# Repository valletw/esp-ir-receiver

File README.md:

# ESP32 Infra-Red Receiver

This project is made to receive IR transmitter information (TV remote) and
control something over WiFi. This project will be used for
[UPnP remote controller project](https://github.com/valletw/esp-upnp-remote).

## Hardware

Four status LED are available:

- `PWR`: 3.3V state
- `BT`: Bluetooth / BLE pairing status
- `WIFI`: WiFi connection status
- `STAT`: Software protocol status

Two buttons are available:

- `BOOT`: Control processor download mode on boot
- `EN`: Control processor reset

For advanced debug, test points are available for JTAG probe and UART controller.

*Note: 3D shapes were not fully configured on my setup, so some components are not
displayed in the render, to be fix.*

### Components choice

This project is based on an ESP32-C3 SoC: `ESP8685H4` (4 MB Flash with no
PSRAM). ESP32 has been selected for the WiFi & Bluetooth support and the big
community to generate easily a software. The choice of "C3" is to ensure support
with the SDK for longer time and minimal footprint. ESP32 modules have not been
kept due to PCB assembly fees. Espressif hardware design rules has been take into
account following there
[documentation](https://docs.espressif.com/projects/esp-hardware-design-guidelines/en/latest/esp32c3/pcb-layout-design.html)

USB-UART bridge has not been added to reduce the number of component. The ESP32
support direct USB connection to manage debug mode with firmware download, and
UART communication.

The 3.3V to power all the components is generated from an LDO using the 5V of the
USB socket.

All others components has been selected from [JLCPCB](https://jlcpcb.com/parts/)
catalogue to minimize the cost and the assembly fees.

### Manufacturing

The board is manufactured by [JLCPCB](https://jlcpcb.com), here is the details
you will require to generate an order.

*Note: JLCPCB requests some modifications on output files, do not use direct
export from KiCad (check the FAQ)*

#### PCB

Files: [Gerbers](jlcpcb/gerbers.zip)

Configuration              | Value
---------------------------|---------------------------------
Base Materiel              | FR-4
Layers                     | 4
Dimensions                 | 33.14 x 21.45
Different design           | 1
Delivery format            | Single PCB
PCB thickness              | 1.6
PCB color                  | Green (other colors have fees)
Silkscreen                 | White
Materiel type              | FR4-Standard TG 135-140
Surface finish             | HASL
Specify layer sequence     | F_Cu / In1_Cu / In2_Cu / B_Cu
Impedance control          | Yes
Layer stack-up             | JLC04161H-7628
Via covering               | Tented or Plugged
Min via hole size/diameter | 0.3mm/0.4mm
Remove order number        | Specify a location

*Note: All options have not been detail here, keep default value.*

#### Assembly

Files: [BOM](jlcpcb/bom.csv), [CPL](jlcpcb/cpl.csv)

Configuration       | Value
--------------------|--------------------
PCBA type           | Economic
Assembly side       | Top
Tooling holes       | Added by JLCPCB

Verify "pick & place" orientations and positions on the web viewer

JLCPCB will add 2 tooling holes for assembly (1 mm diameter near the board corners).

*Note: All options have not been detail here, keep default value.*

### ESP32 Pinout

For those who want to reuse this project, here is the ESP32 pinout to manage the
different input/output.

Name              | Pin  | Direction
------------------|------|----------
IR Rx             | IO3  | Input
WiFi status       | IO0  | Output
Bluetooth status  | IO1  | Output
Software status   | IO10 | Output

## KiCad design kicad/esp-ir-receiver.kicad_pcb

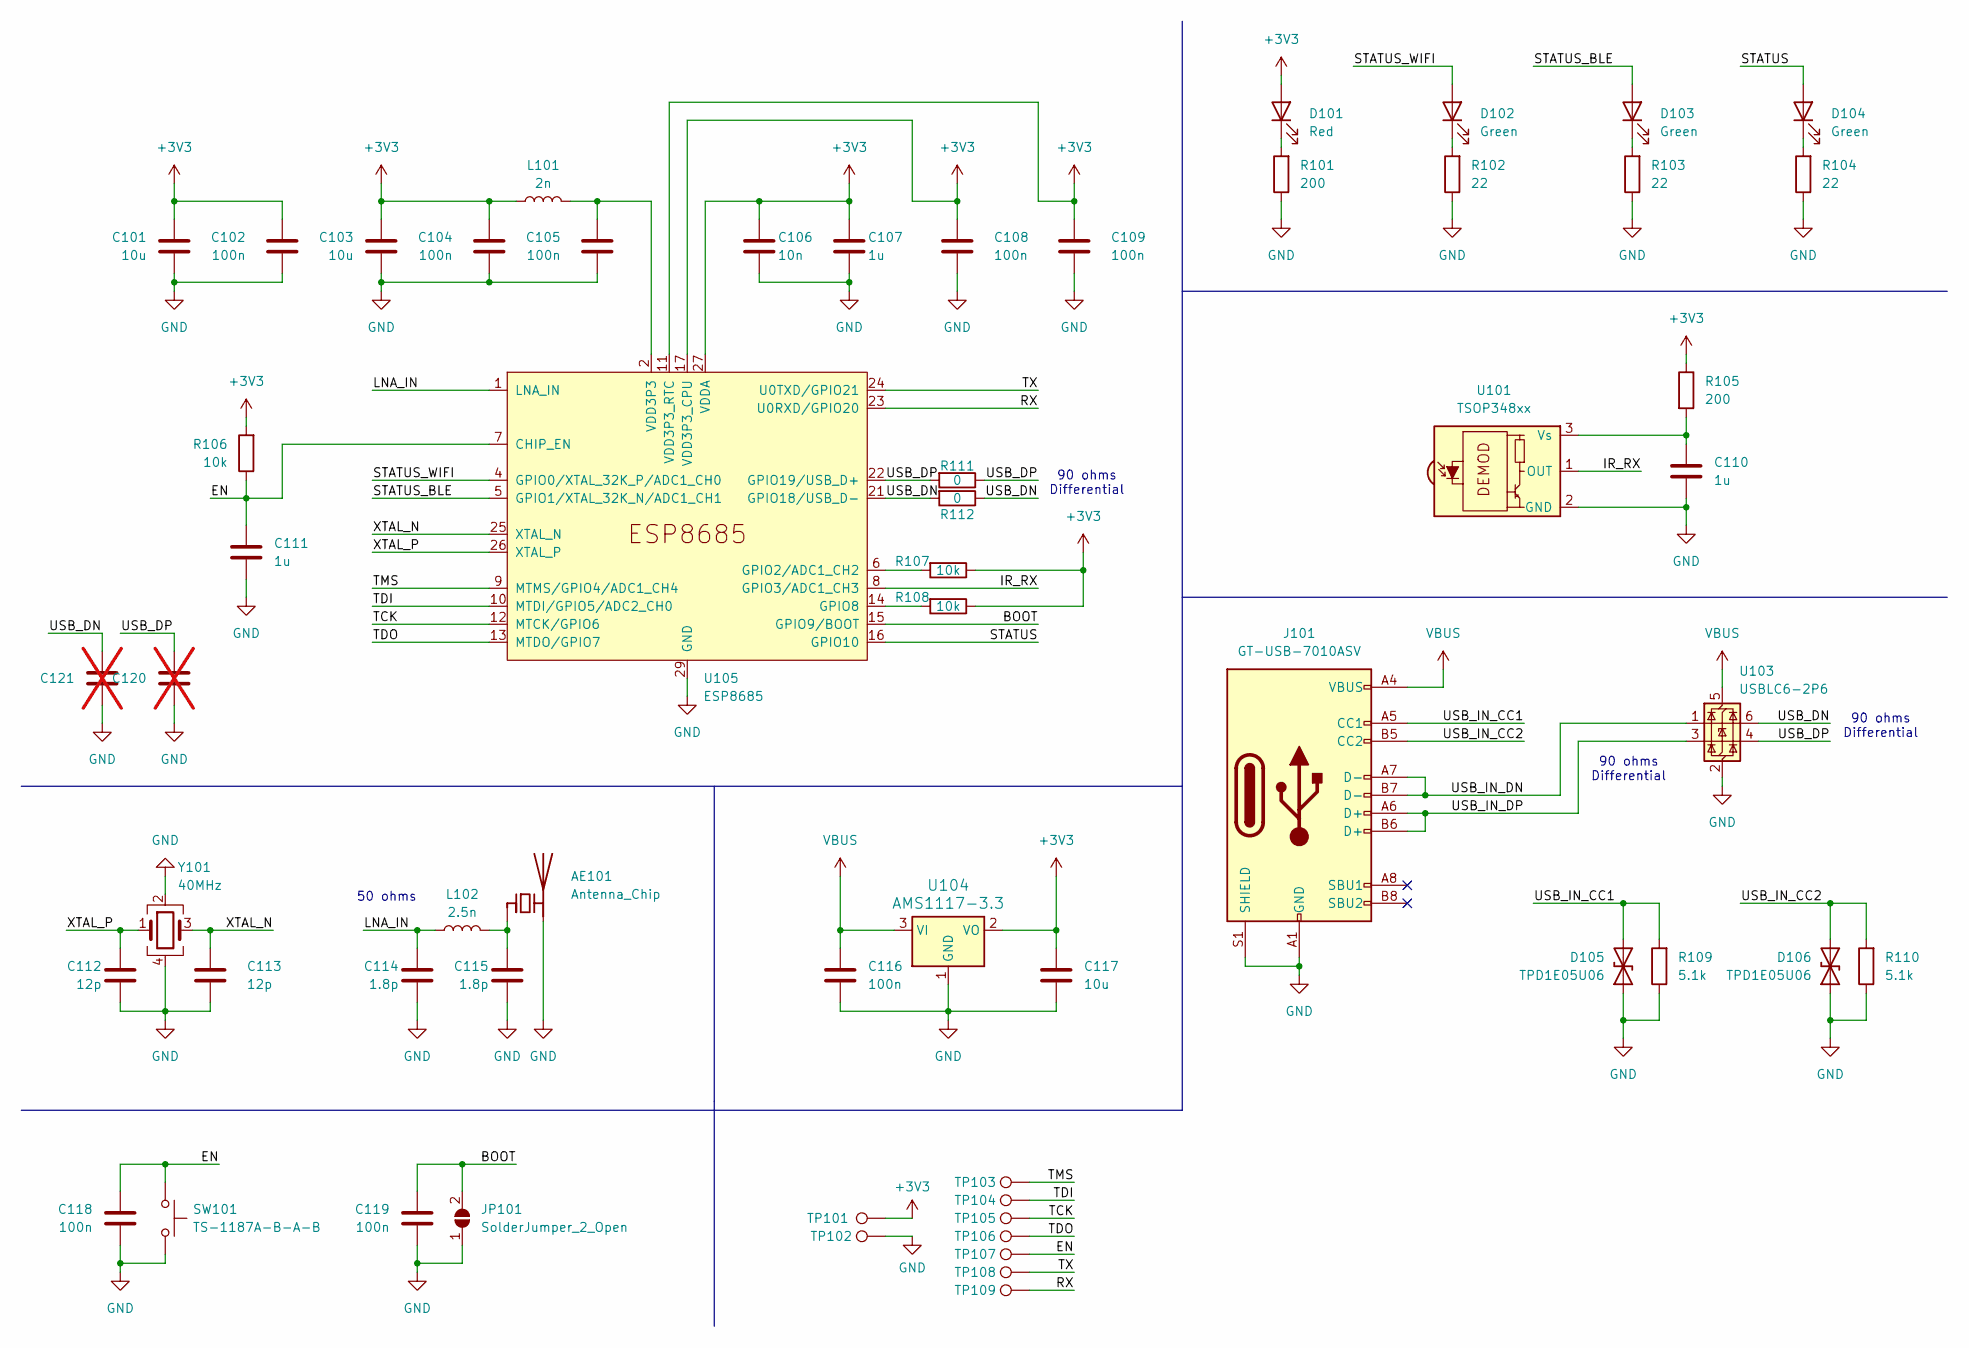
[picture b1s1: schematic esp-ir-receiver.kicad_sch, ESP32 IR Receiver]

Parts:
AE101: Antenna_Chip; Texas_SWRA117D_2.4GHz_Left
C101, C103, C117: 10u; C_0402_1005Metric; MFR Part# CL05A106MQ5NUNC; JLCPCB Part# C15525
C102, C104, C105, C108, C109, C116, C118, C119: 100n; C_0402_1005Metric; MFR Part# CL05B104KO5NNNC; JLCPCB Part# C1525
C106: 10n; C_0402_1005Metric; MFR Part# CL05B103KB5NNNC; JLCPCB Part# C15195
C107, C110, C111: 1u; C_0402_1005Metric; MFR Part# CL05A105KA5NQNC; JLCPCB Part# C52923
C112, C113: 12p; C_0402_1005Metric; MFR Part# 0402CG120J500NT; JLCPCB Part# C1547
C114, C115: 1.8p; C_0402_1005Metric; MFR Part# 0402CG1R8C500NT; JLCPCB Part# C1553
C120, C121: C_0402_1005Metric; not fitted
D101: Red; LED_0603_1608Metric; MFR Part# KT-0603R; JLCPCB Part# C2286
D102, D103, D104: Green; LED_0603_1608Metric; MFR Part# 19-217/GHC-YR1S2/3T; JLCPCB Part# C72043
D105, D106: TPD1E05U06; Texas_DPY0002A_0.6x1mm_P0.65mm; MFR Part# TPD1E05U06DPYR; JLCPCB Part# C436349
J101: GT-USB-7010ASV; USB_C_Receptacle_G-Switch_GT-USB-7010ASV; MFR Part# GT-USB-7010ASV; JLCPCB Part# C2988369
JP101: SolderJumper_2_Open; SolderJumper-2_P1.3mm_Open_RoundedPad1.0x1.5mm
L101: 2n; L_0402_1005Metric; MFR Part# LQG15HS2N0S02D; JLCPCB Part# C18216
L102: 2.5n; L_0402_1005Metric; MFR Part# LQW15AN2N5B00D; JLCPCB Part# C237342
R101, R105: 200; R_0402_1005Metric; MFR Part# 0402WGF2000TCE; JLCPCB Part# C25087
R102, R103, R104: 22; R_0402_1005Metric; MFR Part# 0402WGF220JTCE; JLCPCB Part# C25092
R106, R107, R108: 10k; R_0402_1005Metric; MFR Part# 0402WGF1002TCE; JLCPCB Part# C25744
R109, R110: 5.1k; R_0402_1005Metric; MFR Part# 0402WGF5101TCE; JLCPCB Part# C25905
R111, R112: 0; R_0402_1005Metric; MFR Part# 0402WGF0000TCE; JLCPCB Part# C17168
SW101: TS-1187A-B-A-B; SW_Push_1P1T_XKB_TS-1187A; MFR Part# TS-1187A-B-A-B; JLCPCB Part# C318884
TP101: 3V3; TestPoint_Pad_D1.0mm
TP102: GND; TestPoint_Pad_1.0x1.0mm
TP103: TMS; TestPoint_Pad_D1.0mm
TP104: TDI; TestPoint_Pad_D1.0mm
TP105: TCK; TestPoint_Pad_D1.0mm
TP106: TDO; TestPoint_Pad_D1.0mm
TP107: RST; TestPoint_Pad_D1.0mm
TP108: TX; TestPoint_Pad_D1.0mm
TP109: RX; TestPoint_Pad_D1.0mm
U101: TSOP348xx; Vishay_MOLD-3Pin; MFR Part# TSOP34838; JLCPCB Part# C44620
U103: USBLC6-2P6; SOT-666; MFR Part# USBLC6-2P6; JLCPCB Part# C15999
U104: AMS1117-3.3; SOT-223; MFR Part# AMS1117-3.3; JLCPCB Part# C6186
U105: ESP8685; QFN-28-1EP_4x4mm_P0.4mm_EP2.6x2.6mm; MFR Part# ESP8685H4; JLCPCB Part# C4944062
Y101: 40MHz; Crystal_SMD_3225-4Pin_3.2x2.5mm; MFR Part# K3A4000010.510; JLCPCB Part# C2875582

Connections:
+3V3: C101.1, C102.2, C103.1, C104.2, C106.2, C107.2, C108.2, C109.2, C117.1, D101.2 (A), L101.2, R105.1, R106.2, R107.1, R108.1, TP101.1, U104.2 (VO), U105.11 (VDD3P3_RTC), U105.17 (VDD3P3_CPU), U105.27 (VDDA), U105.28 (VDDA)
/BOOT: C119.1, JP101.2 (B), U105.15 (GPIO9/BOOT)
/EN: C111.2, C118.1, R106.1, SW101.1, TP107.1, U105.7 (CHIP_EN)
/IR_RX: U101.1 (OUT), U105.8 (GPIO3/ADC1_CH3)
/LNA_IN: C114.1, L102.1, U105.1 (LNA_IN)
/RX: TP109.1, U105.23 (U0RXD/GPIO20)
/STATUS: D104.2 (A), U105.16 (GPIO10)
/STATUS_BLE: D103.2 (A), U105.5 (GPIO1/XTAL_32K_N/ADC1_CH1)
/STATUS_WIFI: D102.2 (A), U105.4 (GPIO0/XTAL_32K_P/ADC1_CH0)
/TCK: TP105.1, U105.12 (MTCK/GPIO6)
/TDI: TP104.1, U105.10 (MTDI/GPIO5/ADC2_CH0)
/TDO: TP106.1, U105.13 (MTDO/GPIO7)
/TMS: TP103.1, U105.9 (MTMS/GPIO4/ADC1_CH4)
/TX: TP108.1, U105.24 (U0TXD/GPIO21)
/USB_DN: C121.2, R112.1, R112.2, U103.6 (I/O1), U105.21 (GPIO18/USB_D-)
/USB_DP: C120.2, R111.1, R111.2, U103.4 (I/O2), U105.22 (GPIO19/USB_D+)
/USB_IN_CC1: D105.2 (A2), J101.A5 (CC1), R109.2
/USB_IN_CC2: D106.2 (A2), J101.B5 (CC2), R110.2
/USB_IN_DN: J101.A7 (D-), J101.B7 (D-), U103.1 (I/O1)
/USB_IN_DP: J101.A6 (D+), J101.B6 (D+), U103.3 (I/O2)
/XTAL_N: C113.1, U105.25 (XTAL_N), Y101.3
/XTAL_P: C112.1, U105.26 (XTAL_P), Y101.1
GND: AE101.2 (PCB_Trace), C101.2, C102.1, C103.2, C104.1, C105.1, C106.1, C107.1, C108.1, C109.1, C110.1, C111.1, C112.2, C113.2, C114.2, C115.2, C116.2, C117.2, C118.2, C119.2, C120.1, C121.1, D105.1 (A1), D106.1 (A1), J101.A1 (GND), J101.A12 (GND), J101.B1 (GND), J101.B12 (GND), J101.S1 (SHIELD), JP101.1 (A), R101.1, R102.1, R103.1, R104.1, R109.1, R110.1, SW101.2, TP102.1, U101.2 (GND), U103.2 (GND), U104.1 (GND), U105.29 (GND), Y101.2, Y101.4
unnamed: AE101.1 (FEED), C115.1, L102.2
unnamed: C105.2, L101.1, U105.2 (VDD3P3), U105.3 (VDD3P3)
unnamed: D101.1 (K), R101.2
unnamed: D102.1 (K), R102.2
unnamed: D103.1 (K), R103.2
unnamed: D104.1 (K), R104.2
unnamed: C110.2, R105.2, U101.3 (Vs)
unnamed: R107.2, U105.6 (GPIO2/ADC1_CH2)
unnamed: R108.2, U105.14 (GPIO8)
VBUS: C116.1, J101.A4 (VBUS), J101.A9 (VBUS), J101.B4 (VBUS), J101.B9 (VBUS), U103.5 (VBUS), U104.3 (VI)

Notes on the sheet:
50 ohms
90 ohms Differential

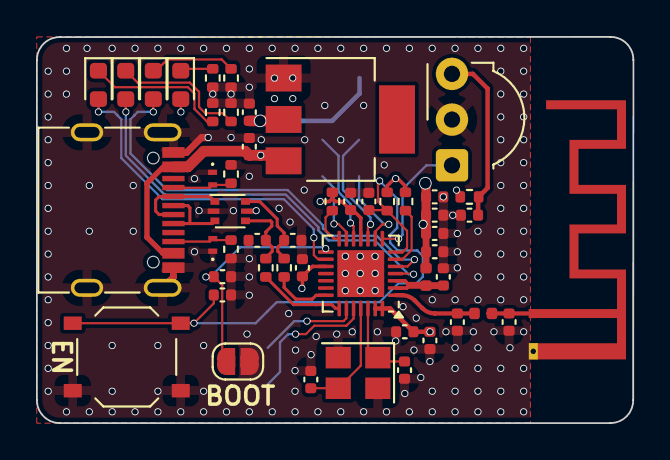
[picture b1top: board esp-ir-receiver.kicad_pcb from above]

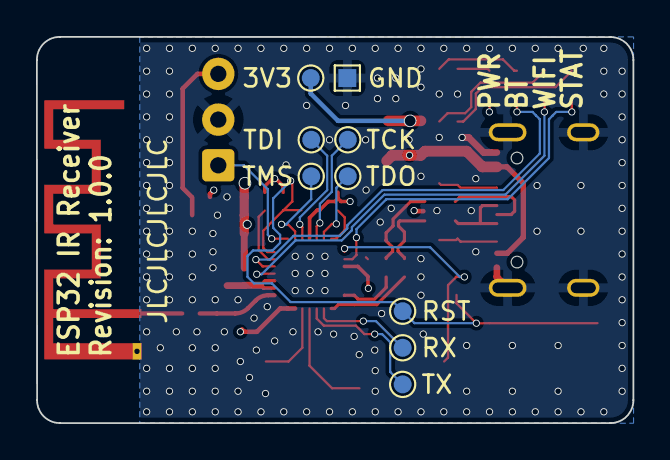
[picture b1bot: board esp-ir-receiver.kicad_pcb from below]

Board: 4 copper layers, 33.1 x 21.5 mm, 59 parts (9 on the bottom side), 33 nets.

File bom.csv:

"Reference","Qty","Value","Footprint","JLCPCB Part#","Manufacturer","MFR Part#"
"C101,C103,C117","3","10u","Capacitor_SMD:C_0402_1005Metric","C15525","Samsung Electro-Mechanics","CL05A106MQ5NUNC"
"C102,C104,C105,C108,C109,C116,C118,C119","8","100n","Capacitor_SMD:C_0402_1005Metric","C1525","Samsung Electro-Mechanics","CL05B104KO5NNNC"
"C106","1","10n","Capacitor_SMD:C_0402_1005Metric","C15195","Samsung Electro-Mechanics","CL05B103KB5NNNC"
"C107,C110,C111","3","1u","Capacitor_SMD:C_0402_1005Metric","C52923","Samsung Electro-Mechanics","CL05A105KA5NQNC"
"C112,C113","2","12p","Capacitor_SMD:C_0402_1005Metric","C1547","FH (Guangdong Fenghua Advanced Tech)","0402CG120J500NT"
"C114,C115","2","1.8p","Capacitor_SMD:C_0402_1005Metric","C1553","FH (Guangdong Fenghua Advanced Tech)","0402CG1R8C500NT"
"D101","1","Red","LED_SMD:LED_0603_1608Metric","C2286","Hubei KENTO Elec","KT-0603R"
"D102,D103,D104","3","Green","LED_SMD:LED_0603_1608Metric","C72043","Everlight Elec","19-217/GHC-YR1S2/3T"
"D105,D106","2","TPD1E05U06","Package_SON:Texas_DPY0002A_0.6x1mm_P0.65mm","C436349","Texas Instruments","TPD1E05U06DPYR"
"J101","1","GT-USB-7010ASV","Connector_USB:USB_C_Receptacle_G-Switch_GT-USB-7010ASV","C2988369","G-Switch","GT-USB-7010ASV"
"L101","1","2n","Inductor_SMD:L_0402_1005Metric","C18216","Murata Electronics","LQG15HS2N0S02D"
"L102","1","2.5n","Inductor_SMD:L_0402_1005Metric","C237342","Murata Electronics","LQW15AN2N5B00D"
"R101,R105","2","200","Resistor_SMD:R_0402_1005Metric","C25087","UNI-ROYAL(Uniroyal Elec)","0402WGF2000TCE"
"R102,R103,R104","3","22","Resistor_SMD:R_0402_1005Metric","C25092","UNI-ROYAL(Uniroyal Elec)","0402WGF220JTCE"
"R106,R107,R108","3","10k","Resistor_SMD:R_0402_1005Metric","C25744","UNI-ROYAL(Uniroyal Elec)","0402WGF1002TCE"
"R109,R110","2","5.1k","Resistor_SMD:R_0402_1005Metric","C25905","UNI-ROYAL(Uniroyal Elec)","0402WGF5101TCE"
"R111,R112","2","0","Resistor_SMD:R_0402_1005Metric","C17168","UNI-ROYAL(Uniroyal Elec)","0402WGF0000TCE"
"SW101","1","TS-1187A-B-A-B","Button_Switch_SMD:SW_Push_1P1T_XKB_TS-1187A","C318884","XKB Connectivity","TS-1187A-B-A-B"
"U101","1","TSOP348xx","OptoDevice:Vishay_MOLD-3Pin","C44620","Vishay Intertech","TSOP34838"
"U103","1","USBLC6-2P6","Package_TO_SOT_SMD:SOT-666","C15999","STMicroelectronics","USBLC6-2P6"
"U104","1","AMS1117-3.3","Package_TO_SOT_SMD:SOT-223","C6186","Advanced Monolithic Systems","AMS1117-3.3"
"U105","1","ESP8685","Package_DFN_QFN:QFN-28-1EP_4x4mm_P0.4mm_EP2.6x2.6mm","C4944062","Espressif","ESP8685H4"
"Y101","1","40MHz","Crystal:Crystal_SMD_3225-4Pin_3.2x2.5mm","C2875582","KYX","K3A4000010.510"

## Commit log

2024-04-19 Initial issue
2024-04-19 Provide KiCad project files
2024-04-19 Provide manufacturing files
2024-04-22 Add README
2024-05-01 Add unboxed image

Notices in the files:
kicad/esp-ir-receiver.kicad_pcb:
MIT License
